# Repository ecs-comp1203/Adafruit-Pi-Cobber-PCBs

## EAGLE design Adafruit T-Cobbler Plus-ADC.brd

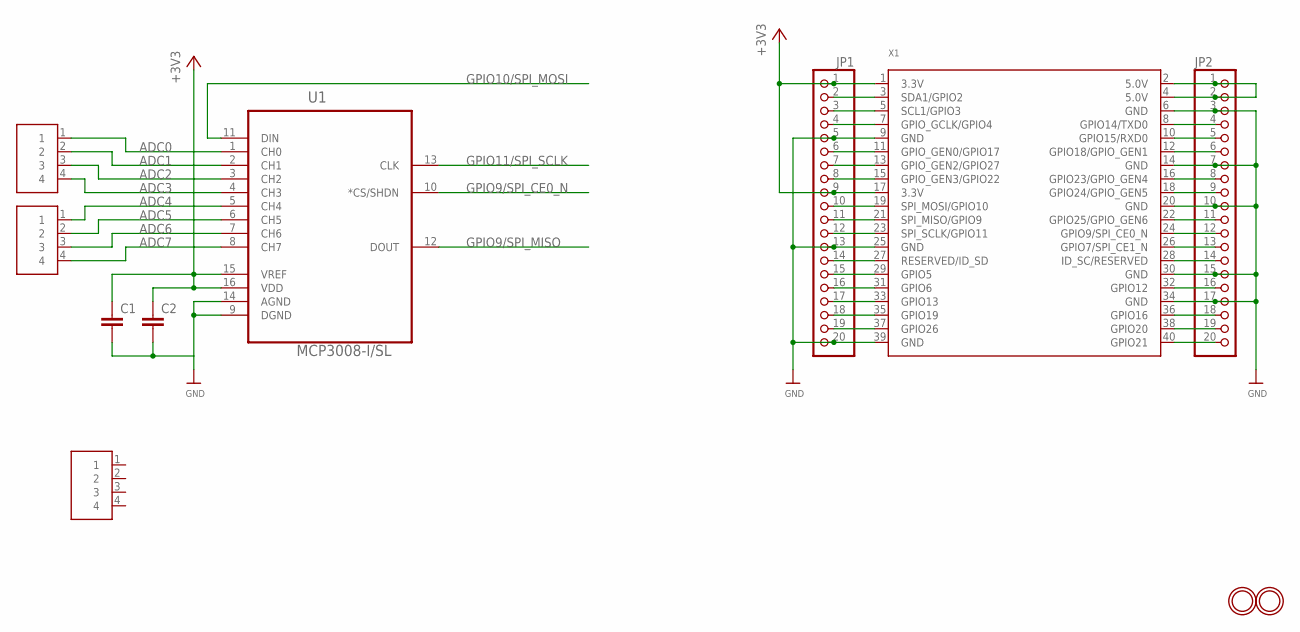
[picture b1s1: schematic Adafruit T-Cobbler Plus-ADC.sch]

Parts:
C1, C2: C-EUC0805; C0805
JP1, JP2: HEADER-1X20ROUND; 1X20_ROUND
U1: MCP3008-I/SL; SOIC127P600X175-16N
U$1, U$9, U$10: 1X4THM; 1X4
U$2, U$4: MOUNTINGHOLE2.5_THICK; MOUNTINGHOLE_2.5_PLATED_THICK
X1: RASPBERRYPI_B+_IDC

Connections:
+3V3: C1.1, C2.1, JP1.1, JP1.9, U1.15 (VREF), U1.16 (VDD), X1.1 (3.3V), X1.17 (3.3V)
ADC0: U1.1 (CH0), U$9.1
ADC1: U1.2 (CH1), U$9.2
ADC2: U1.3 (CH2), U$9.3
ADC3: U1.4 (CH3), U$9.4
ADC4: U1.5 (CH4), U$10.1
ADC5: U1.6 (CH5), U$10.2
ADC6: U1.7 (CH6), U$10.3
ADC7: U1.8 (CH7), U$10.4
GND: C1.2, C2.2, JP1.5, JP1.13, JP1.20, JP2.3, JP2.7, JP2.10, JP2.15, JP2.17, U1.9 (DGND), U1.14 (AGND), X1.6 (GND), X1.9 (GND), X1.14 (GND), X1.20 (GND), X1.25 (GND), X1.30 (GND), X1.34 (GND), X1.39 (GND)
GPIO7/SPI_CE1_N: JP2.13, X1.26 (GPIO7/SPI_CE1_N)
GPIO9/SPI_CE0_N: JP2.12, U1.10 (*CS/SHDN), X1.24 (GPIO9/SPI_CE0_N)
GPIO9/SPI_MISO: JP1.11, U1.12 (DOUT), X1.21 (SPI_MISO/GPIO9)
GPIO10/SPI_MOSI: JP1.10, U1.11 (DIN), X1.19 (SPI_MOSI/GPIO10)
GPIO11/SPI_SCLK: JP1.12, U1.13 (CLK), X1.23 (SPI_SCLK/GPIO11)
unnamed: JP2.1, JP2.2, X1.2 (5.0V), X1.4 (5.0V)
unnamed: JP2.4, X1.8 (GPIO14/TXD0)
unnamed: JP2.5, X1.10 (GPIO15/RXD0)
unnamed: JP2.6, X1.12 (GPIO18/GPIO_GEN1)
unnamed: JP2.8, X1.16 (GPIO23/GPIO_GEN4)
unnamed: JP2.9, X1.18 (GPIO24/GPIO_GEN5)
unnamed: JP2.11, X1.22 (GPIO25/GPIO_GEN6)
unnamed: JP2.14, X1.28 (ID_SC/RESERVED)
unnamed: JP2.16, X1.32 (GPIO12)
unnamed: JP2.18, X1.36 (GPIO16)
unnamed: JP2.19, X1.38 (GPIO20)
unnamed: JP2.20, X1.40 (GPIO21)
unnamed: JP1.2, X1.3 (SDA1/GPIO2)
unnamed: JP1.3, X1.5 (SCL1/GPIO3)
unnamed: JP1.4, X1.7 (GPIO_GCLK/GPIO4)
unnamed: JP1.6, X1.11 (GPIO_GEN0/GPIO17)
unnamed: JP1.7, X1.13 (GPIO_GEN2/GPIO27)
unnamed: JP1.8, X1.15 (GPIO_GEN3/GPIO22)
unnamed: JP1.14, X1.27 (RESERVED/ID_SD)
unnamed: JP1.15, X1.29 (GPIO5)
unnamed: JP1.16, X1.31 (GPIO6)
unnamed: JP1.17, X1.33 (GPIO13)
unnamed: JP1.18, X1.35 (GPIO19)
unnamed: JP1.19, X1.37 (GPIO26)

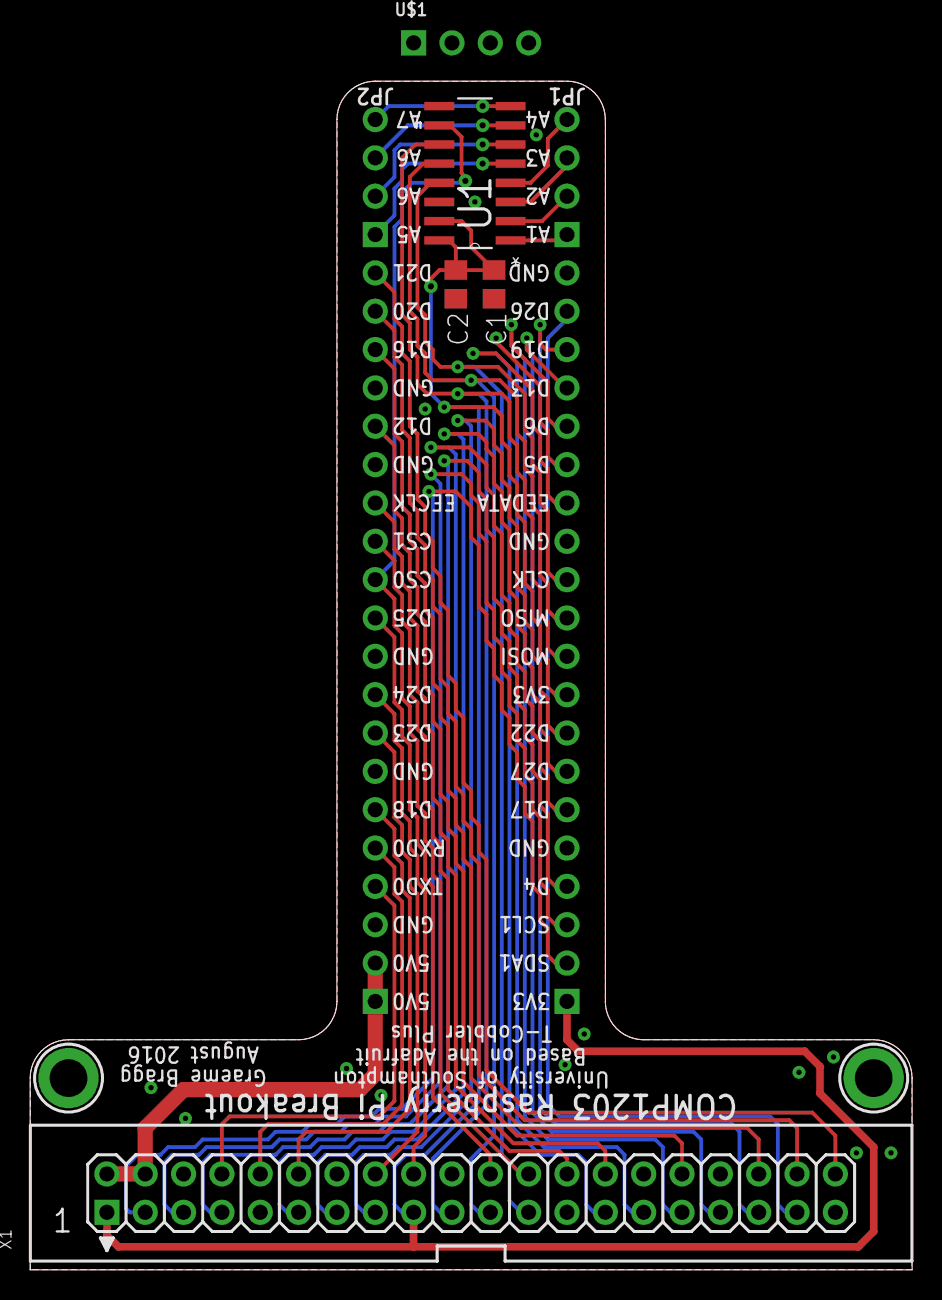
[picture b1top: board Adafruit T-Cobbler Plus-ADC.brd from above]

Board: 2 copper layers, 58.4 x 78.7 mm, 11 parts (0 on the bottom side), 39 nets.

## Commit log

2016-08-12 Added MCP3008 ADC to T-CObbler plus.
    Slimmed down stem to make it sit evenly on the Breadboard.
    Re-ran some tracks.
    Created a parts library

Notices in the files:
parts and their libraries:
microbuilder: This work is placed in the public domain, and may be freely used for commercial and non-commercial work with the following conditions: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
